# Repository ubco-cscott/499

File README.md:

# 499 Capstone Project - Group 16
Connor, Ellis, Nathan, Sarah, Sean

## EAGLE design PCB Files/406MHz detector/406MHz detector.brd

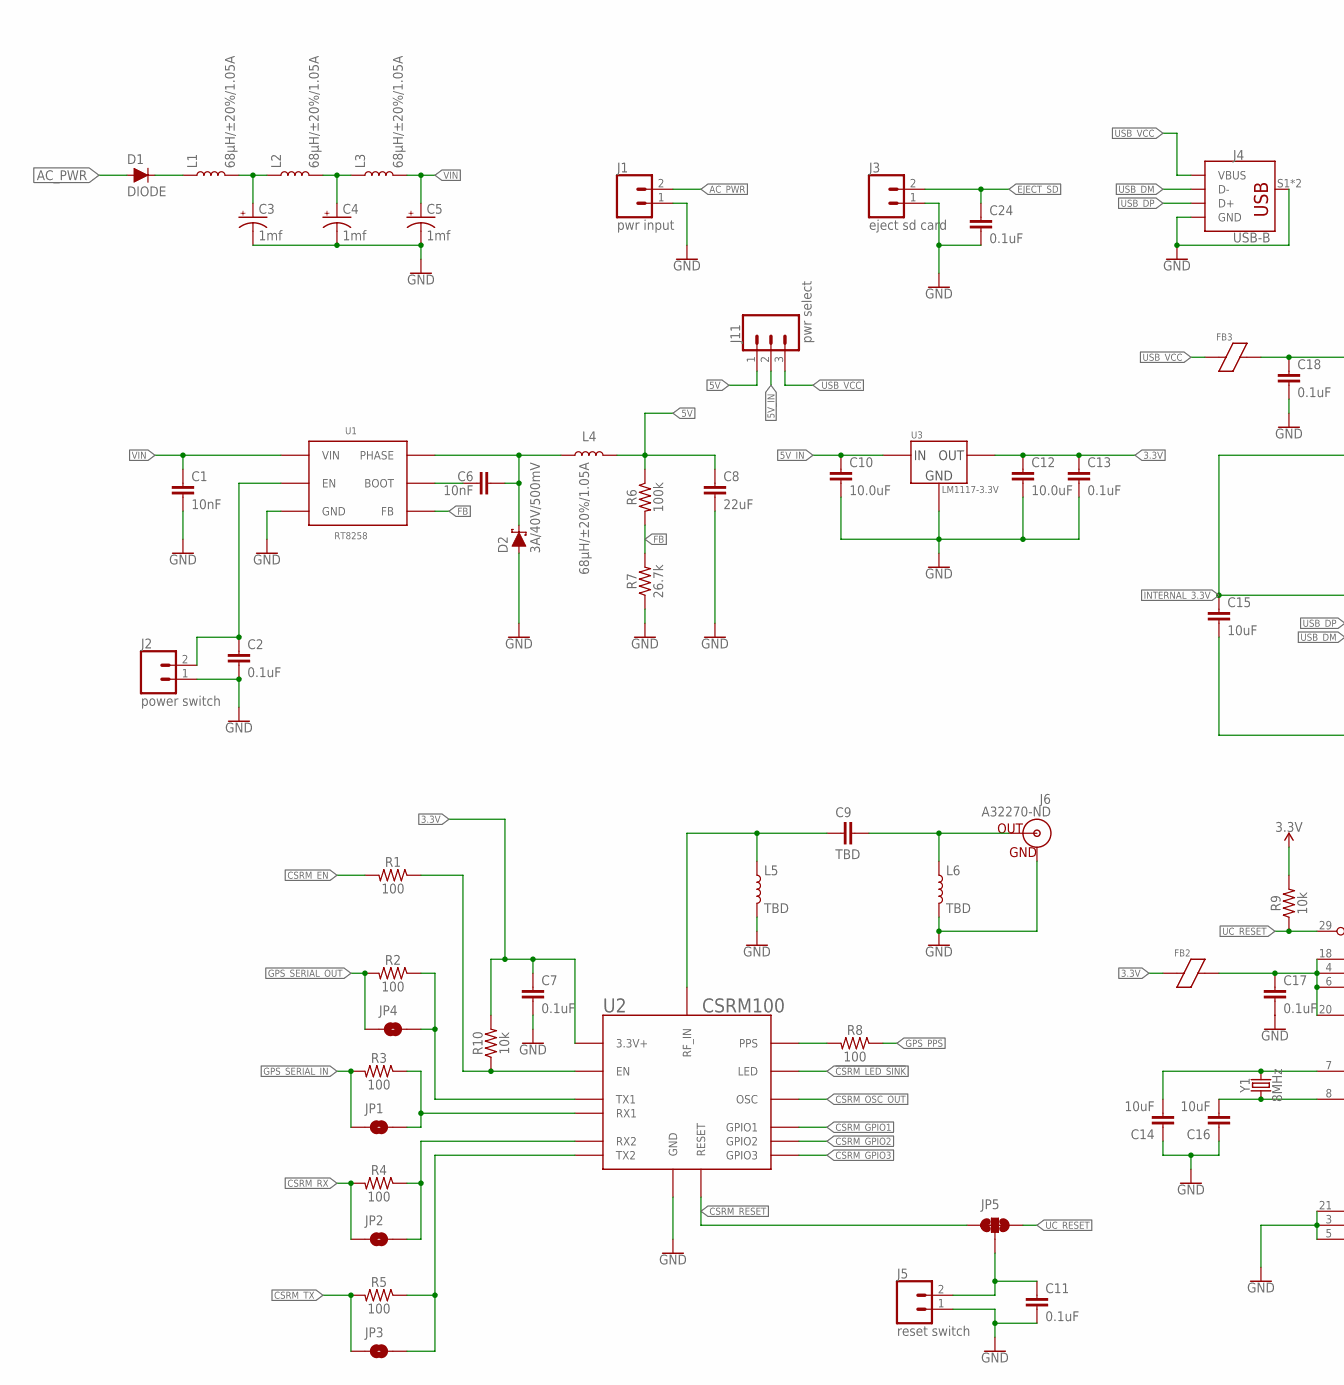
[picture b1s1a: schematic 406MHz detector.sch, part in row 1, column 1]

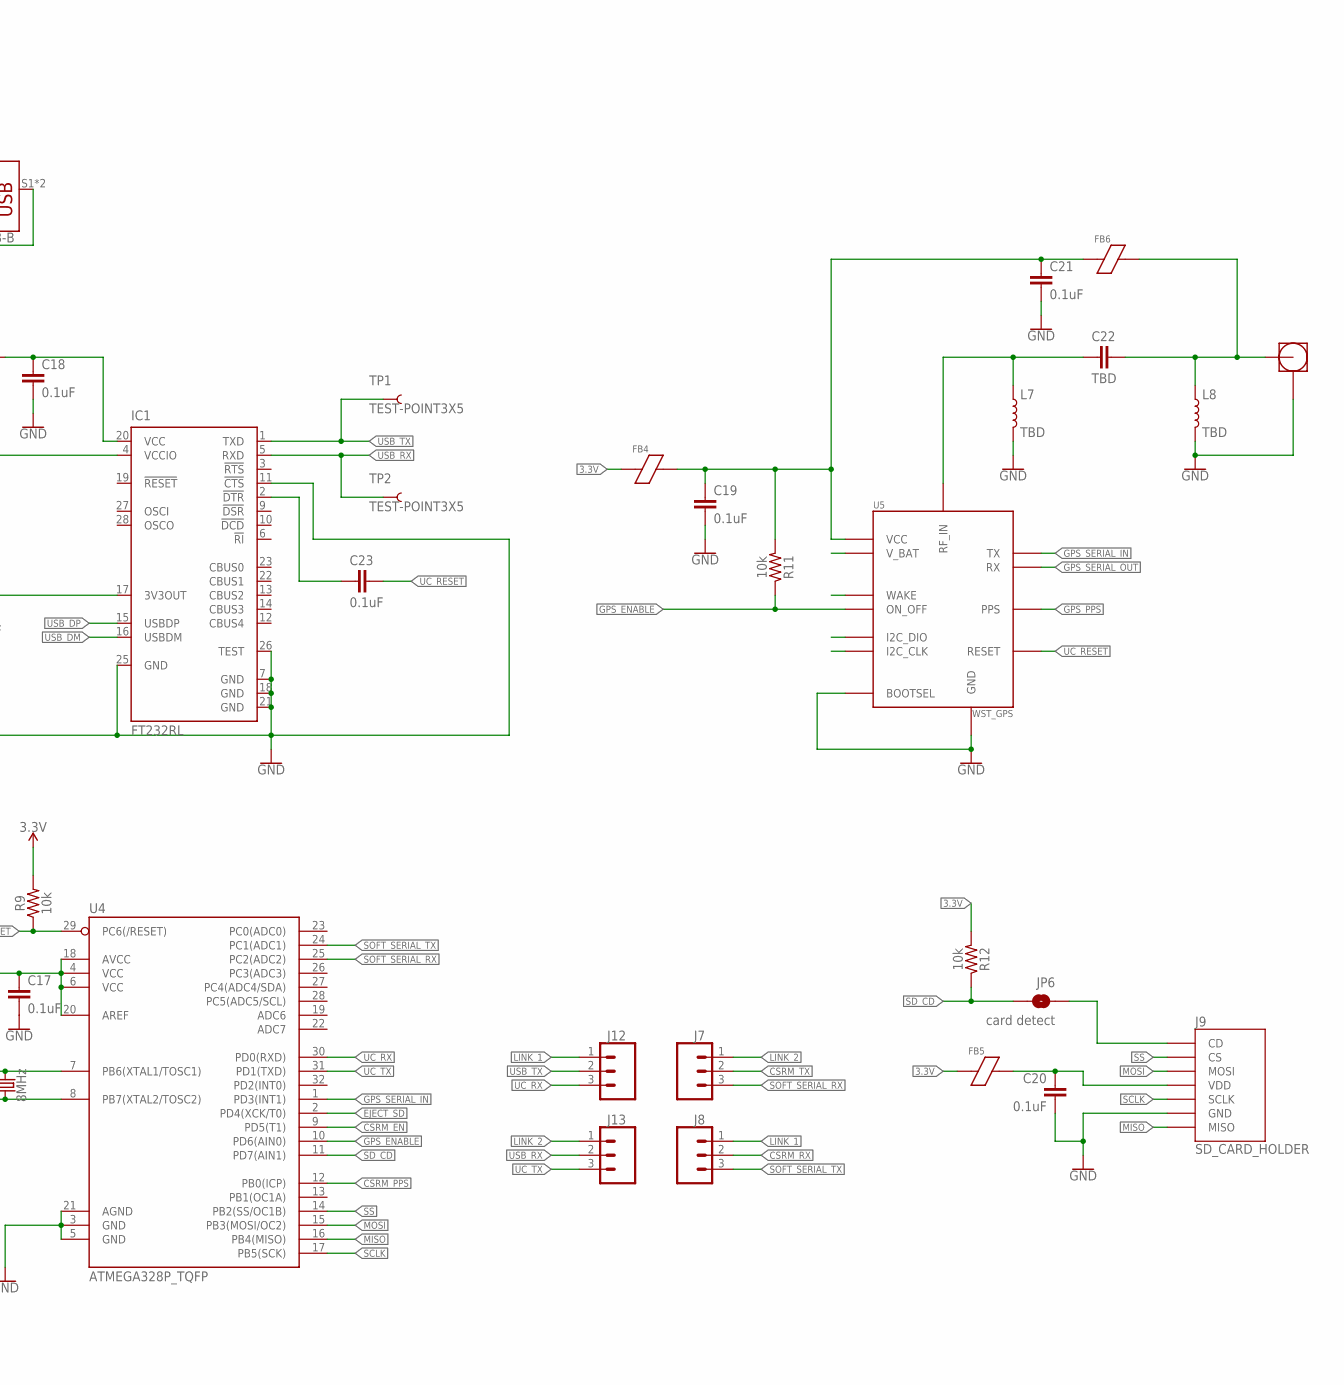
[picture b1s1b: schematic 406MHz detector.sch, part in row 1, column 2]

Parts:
C1, C6: 10nF; 0603
C2, C7, C11, C13, C17, C18, C19, C20, C21, C23, C24: 0.1uF; 0603
C3, C4, C5: 1mf; CPOL-RADIAL-5MM-10MM-KIT
C8: 22uF; 0603
C9, C22: TBD; 0603
C10, C12: 10.0uF; 1206
C14, C15, C16: 10uF; 1206
D1: DIODE; SMA-DIODE
D2: 3A/40V/500mV; SMA-DIODE
FB2, FB3, FB4, FB5, FB6: FERRITE_BEAD; 0603
IC1: FT232RL; SSOP28
J1: pwr input; 1X02_LOCK
J2: power switch; 1X02
J3: eject sd card; 1X02
J4: USB-B; USB
J5: reset switch; 1X02
J6: A32270-ND; A33270-ND
J7, J8, J12, J13: select jumper; 1X03_LOCK
J9: SD_CARD_HOLDER
J10: SMA; SMA_R/A
J11: pwr select; 1X03_LOCK
JP1, JP2, JP3, JP4: JUMPER-SMT_2_NO_SILK_ROUND; SMT-JUMPER_2_NO_SILK_ROUND
JP5: JUMPER-SMT_3_2-NC_TRACE_SILK; SMT-JUMPER_3_2-NC_TRACE_SILK
JP6: card detect; SMT-JUMPER_2_NO_SILK
L1, L2, L3, L4: 68µH/±20%/1.05A; CR75
L5, L6, L7, L8: TBD; 0603
R1, R2, R3, R4, R5, R8: 100; 0603
R6: 100k; 0603
R7: 26.7k; 0603
R9, R10, R11, R12: 10k; 0603
TP1, TP2: TEST-POINT3X5; PAD.03X.05
U1: RT8258; SOT23-6
U2: CSRM100; CSRM
U3: LM1117-3.3V; SOT223
U4: ATMEGA328P_TQFP; TQFP32-08
U5: WST_GPS
Y1: 8MHz; HC49UP

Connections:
3.3V: C7.1, C12.1, C13.1, FB2.1, FB4.1, FB5.1, R9.2, R10.2, R12.2, U2.PWR_IN (3.3V+), U3.2 (VOUT), U3.4 (VOUT)
5V: C8.1, J11.1, L4.P$2 (2), R6.1
5V_IN: C10.1, J11.2, U3.3 (VIN)
406_IN: C9.2, L5.1, U2.406_IN (RF_IN)
!CSRM_LED_SINK: U2.LED
AC_PWR: D1.A, J1.2
ANTENNA_CONNECTOR: C9.1, J6.OUT, L6.1
BOOT: C6.1, U1.1 (BOOT)
CSRM_EN: R1.2, U4.9 (PD5(T1))
CSRM_GPIO1: U2.GPIO1
CSRM_GPIO2: U2.GPIO2
CSRM_GPIO3: U2.GPIO3
CSRM_OSC_OUT: U2.OSC_OUT (OSC)
CSRM_PPS: R8.2, U2.PPS, U4.12 (PB0(ICP))
CSRM_RESET: JP5.1, U2._RESET (RESET)
CSRM_RX: J8.2, JP2.1, R4.2
CSRM_TX: J7.2, JP3.1, R5.2
EJECT_SD: C24.1, J3.2, U4.2 (PD4(XCK/T0))
FB: R6.2, R7.2, U1.3 (FB)
GND: C1.2, C2.2, C3.-, C4.-, C5.-, C7.2, C8.2, C10.2, C11.2, C12.2, C13.2, C14.1, C15.2, C16.1, C17.2, C18.2, C19.2, C20.2, C21.2, C24.2, D2.A, IC1.7 (GND), IC1.11 (!CTS), IC1.18 (GND), IC1.21 (GND), IC1.25 (GND), IC1.26 (TEST), J1.1, J2.1, J3.1, J4.4 (GND), J4.S1 (SHIELD), J4.S2 (SHIELD), J5.1, J6.GND1 (GND), J6.GND2 (GND), J6.GND3 (GND), J6.GND4 (GND), J9.GND1 (GND), J9.GND2 (GND), J9.P6 (GND), J10.P$2, J10.P$3, J10.P$4, J10.P$5, L5.2, L6.2, L7.2, L8.2, R7.1, U1.2 (GND), U2.GND, U2.GND1 (GND), U2.GND2 (GND), U2.GND3 (GND), U2.GND4 (GND), U3.1 (GND), U4.3 (GND), U4.5 (GND), U4.21 (AGND), U5.P$1 (GND), U5.P$3 (GND), U5.P$9 (BOOTSEL), U5.P$17 (GND), U5.P$18 (GND), U5.P$19 (GND)
GPS_ANTENNA: C22.2, L7.1, U5.P$2 (RF_IN)
GPS_CONNECTOR: C22.1, FB6.2, J10.P$1, L8.1
GPS_ENABLE: R11.1, U4.10 (PD6(AIN0)), U5.P$15 (ON_OFF)
GPS_PPS: R8.1, U5.P$14 (PPS)
GPS_SERIAL_IN: JP1.1, R3.2, U4.1 (PD3(INT1)), U5.P$10 (TX)
GPS_SERIAL_OUT: JP4.1, R2.2, U5.P$11 (RX)
HF_SWITCH: C6.2, D2.C, L4.P$1 (1), U1.6 (PHASE)
INTERNAL_3.3V: C15.1, IC1.4 (VCCIO), IC1.17 (3V3OUT)
LINK_1: J8.1, J12.1
LINK_2: J7.1, J13.1
MISO: J9.P7 (MISO), U4.16 (PB4(MISO))
MOSI: J9.P3 (MOSI), U4.15 (PB3(MOSI/OC2))
unnamed: JP4.2, R2.1, U2.TX1
unnamed: JP1.2, R3.1, U2.RX1
unnamed: JP2.2, R4.1, U2.RX2
unnamed: JP3.2, R5.1, U2.TX2
unnamed: R1.1, R10.1, U2.EN
unnamed: C23.1, IC1.2 (!DTR)
unnamed: J9.CD1 (CD), J9.CD2 (CD), JP6.1
unnamed: D1.C, L1.P$1 (1)
unnamed: C3.+, L1.P$2 (2), L2.P$1 (1)
unnamed: C4.+, L2.P$2 (2), L3.P$1 (1)
unnamed: C18.1, FB3.1, IC1.20 (VCC)
unnamed: C14.2, U4.7 (PB6(XTAL1/TOSC1)), Y1.2
unnamed: C16.2, U4.8 (PB7(XTAL2/TOSC2)), Y1.1
unnamed: C19.1, C21.1, FB4.2, FB6.1, R11.2, U5.P$5 (VCC)
unnamed: C17.1, FB2.2, U4.4 (VCC), U4.6 (VCC), U4.18 (AVCC), U4.20 (AREF)
unnamed: C20.1, FB5.2, J9.P4 (VDD)
RESET: C11.1, J5.2, JP5.2
SCLK: J9.P5 (SCLK), U4.17 (PB5(SCK))
SD_CD: JP6.2, R12.1, U4.11 (PD7(AIN1))
SOFT_SERIAL_RX: J7.3, U4.25 (PC2(ADC2))
SOFT_SERIAL_TX: J8.3, U4.24 (PC1(ADC1))
SS: J9.P2 (CS), U4.14 (PB2(SS/OC1B))
SUPPLY_ENABLE: C2.1, J2.2, U1.4 (EN)
UC_RESET: C23.2, JP5.3, R9.1, U4.29 (PC6(/RESET)), U5.P$4 (RESET)
UC_RX: J12.3, U4.30 (PD0(RXD))
UC_TX: J13.3, U4.31 (PD1(TXD))
USB_DM: IC1.16 (USBDM), J4.2 (D-)
USB_DP: IC1.15 (USBDP), J4.3 (D+)
USB_RX: IC1.5 (RXD), J13.2, TP2.P$1
USB_TX: IC1.1 (TXD), J12.2, TP1.P$1
USB_VCC: FB3.2, J4.1 (VBUS), J11.3
VIN: C1.1, C5.+, L3.P$2 (2), U1.5 (VIN)

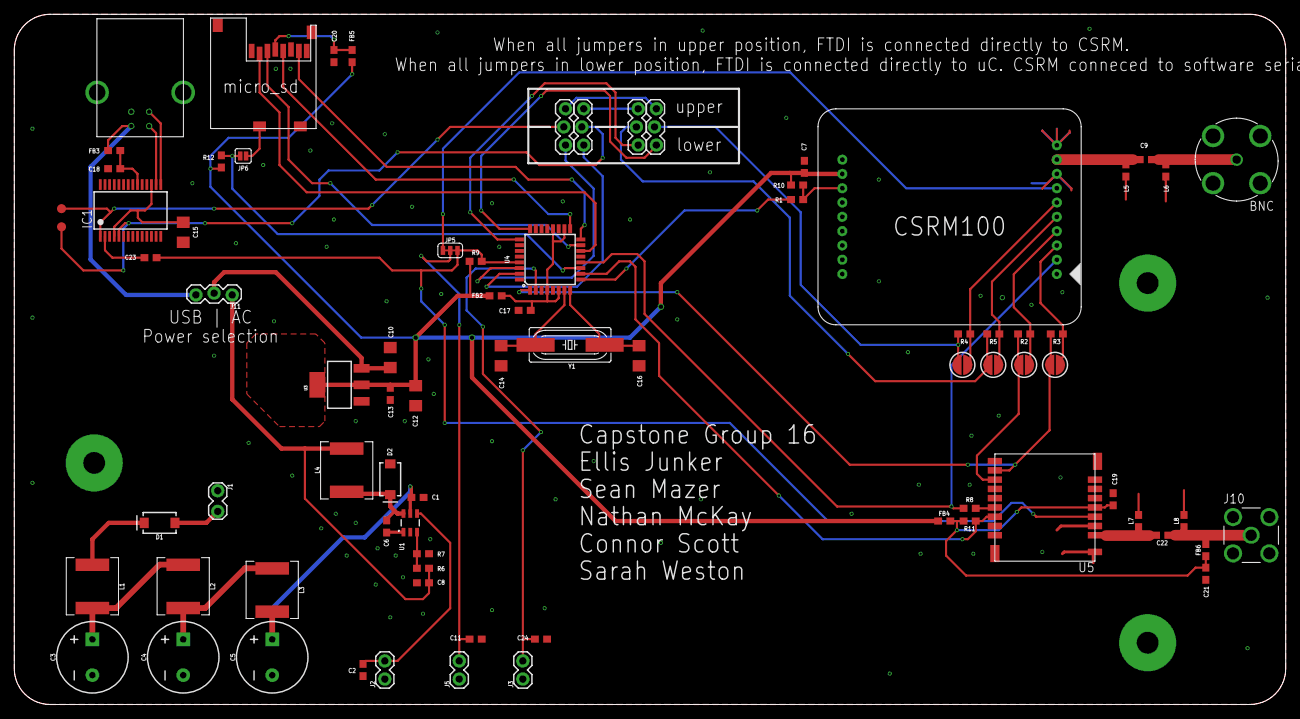
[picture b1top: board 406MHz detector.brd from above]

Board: 2 copper layers, 177.8 x 96.5 mm, 79 parts (0 on the bottom side), 59 nets.

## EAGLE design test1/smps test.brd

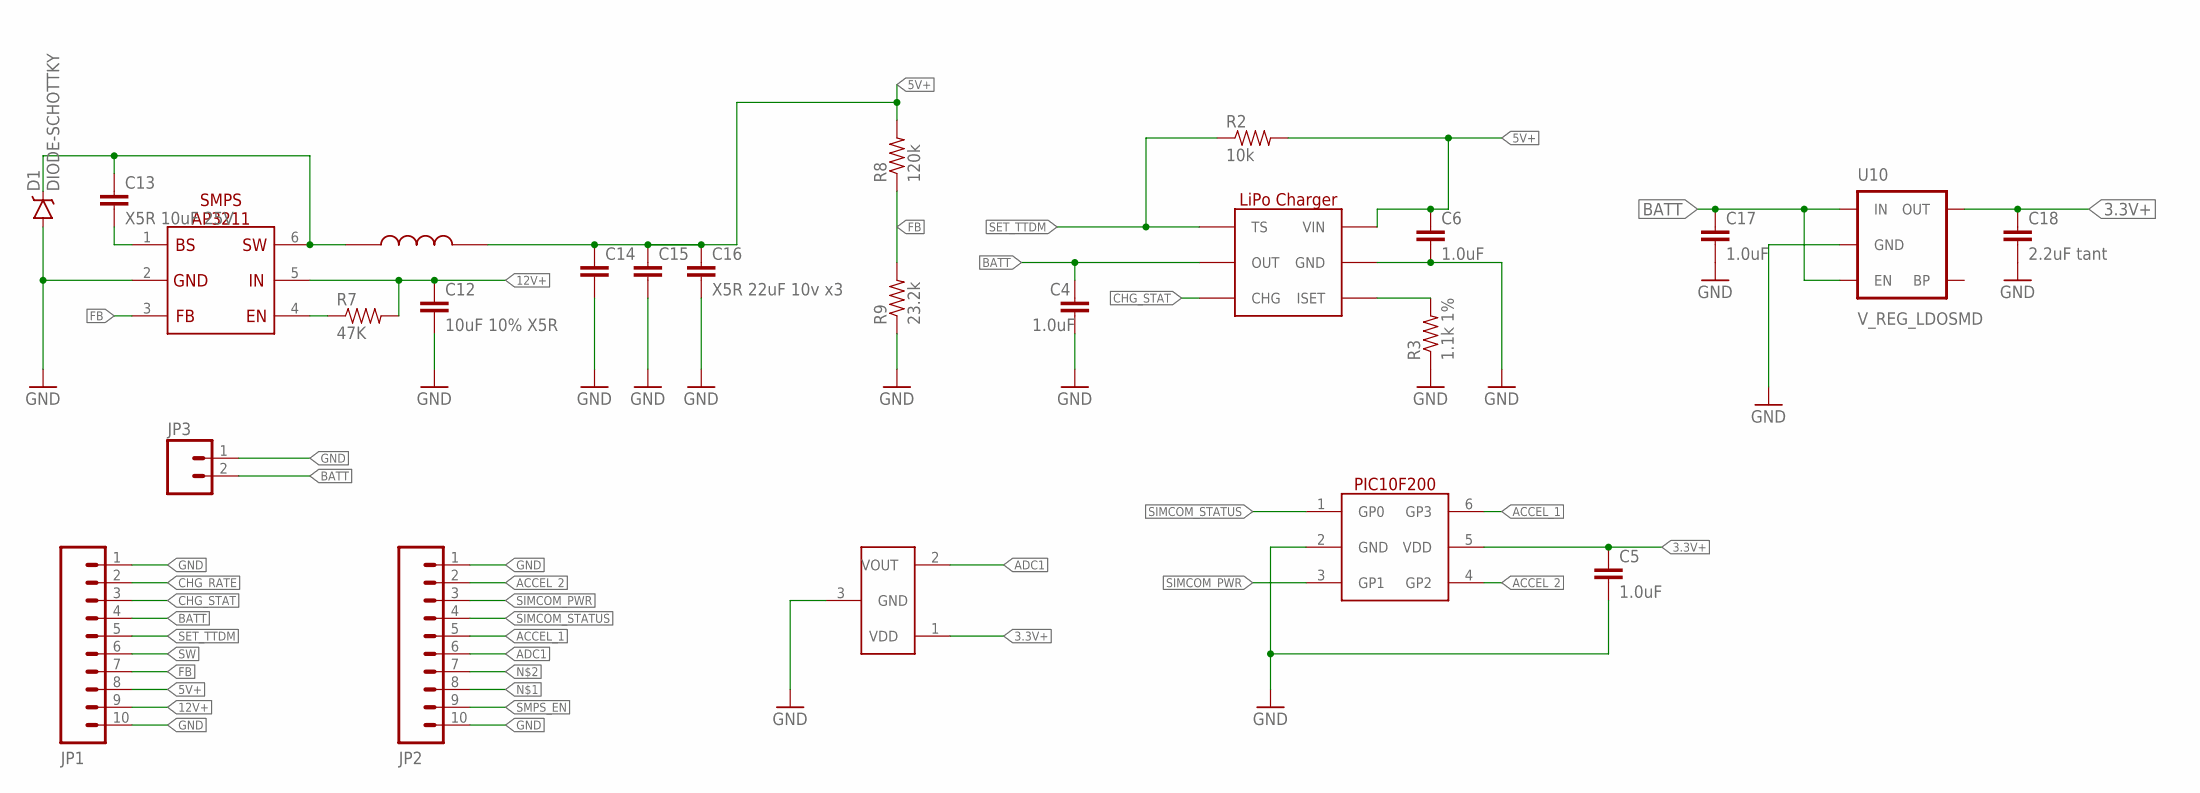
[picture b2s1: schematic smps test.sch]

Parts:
C4, C5, C6, C17: 1.0uF; 0603-CAP
C12: 10uF 10% X5R; 1206
C13: X5R 10uF 25V; 0603-CAP
C14, C15: CAP0603-CAP; 0603-CAP
C16: X5R 22uF 10v x3; 0603-CAP
C18: 2.2uF tant; 0603-CAP
D1: DIODE-SCHOTTKY; MICRO_SMP
JP1, JP2: M10LOCK; 1X10_LOCK
JP3: M02-JST-2MM-SMT; JST-2-SMD
R2: 10k; 0603-RES
R3: 1.1k 1%; 0603-RES
R7: 47K; 0603-RES
R8: 120k; 0603-RES
R9: 23.2k; 0603-RES
U3: BQ21040; SOT23-6
U6: PIC10F200; SOT23-6
U10: V_REG_LDOSMD; SOT23-5
U$1: MCP9700T-E; SOT23-3
U$2: AP3211; SOT23-6
U$4: INDUCTOR; INDUCTOR_FIXED

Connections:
3.3V+: C5.1, C18.1, U6.5 (VDD), U10.5 (OUT), U$1.1 (VDD)
5V+: C6.1, C14.1, C15.1, C16.1, JP1.8, R2.2, R8.2, U3.6 (VIN), U$4.P$2
12V+: C12.1, JP1.9, R7.2, U$2.5
ACCEL_1: JP2.5, U6.6 (GP3)
ACCEL_2: JP2.2, U6.4 (GP2)
ADC1: JP2.6, U$1.2 (VOUT)
BATT: C4.1, C17.1, JP1.4, JP3.2 (1), U3.2 (OUT), U10.1 (IN), U10.3 (EN)
CHG_RATE: JP1.2, R3.2, U3.4 (ISET)
CHG_STAT: JP1.3, U3.3 (CHG)
FB: JP1.7, R8.1, R9.2, U$2.3
GND: C4.2, C5.2, C6.2, C12.2, C14.2, C15.2, C16.2, C17.2, C18.2, D1.P$2 (A), JP1.1, JP1.10, JP2.1, JP2.10, JP3.1 (2), R3.1, R9.1, U3.5 (GND), U6.2 (GND), U10.2 (GND), U$1.3 (GND), U$2.2
unnamed: C13.2, U$2.1
SET_TTDM: JP1.5, R2.1, U3.1 (TS)
SIMCOM_PWR: JP2.3, U6.3 (GP1)
SIMCOM_STATUS: JP2.4, U6.1 (GP0)
SMPS_EN: JP2.9, R7.1, U$2.4
SW: C13.1, D1.P$1 (C), JP1.6, U$2.6, U$4.P$1

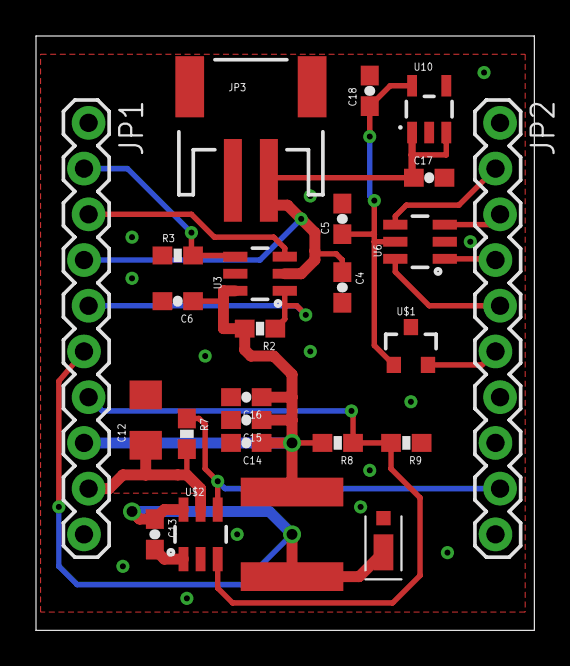
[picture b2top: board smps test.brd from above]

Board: 2 copper layers, 27.7 x 33.0 mm, 25 parts (0 on the bottom side), 17 nets.

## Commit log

2020-01-16 test.txt added
2020-01-16 note
2020-01-19 first update for pull test
2020-01-19 sarahs first change
2020-01-20 first push with real files
2020-01-20 eagle test board added
2020-01-20 changed the name of the example PCB folder
2020-01-21 added the PIC datasheet
2020-01-21 changed the readme
2020-01-21 eagle library and schematic updated
2020-01-21 I started on the converter
2020-01-22 Nathan made changes in 413 lecture finished the converter
2020-01-23 added a package that models the CSRM100 receiver in library labaled capstone L1
2020-01-25 added CSRM100 to capstone library, and schematic
2020-01-26 testing connor's branch
2020-01-26 added branches for Nathan and Sarah
2020-01-26 cleaned up some traces
2020-01-26 cleaning up repo
2020-01-26 fixed ignore files list
2020-01-26 added library backups to ignored files list
2020-01-26 removed library backup files
2020-01-27 added led example
2020-01-27 added a microcontroller
2020-01-27 added led example nets
2020-01-27 nets drawn
2020-01-27 added some nets
2020-01-27 added seperate schematic areas for git merging
2020-01-27 removed sample led changes
2020-01-27 copied from master
2020-01-28 cleaning up branches
2020-01-28 added boxes and labels to schematic for separating workspaces
2020-01-28 removed problem with ground labels connecting to 3.3V net
2020-01-28 added capactior to sw_reg enable input
2020-01-28 added sw_reg datasheet, renamed pic33 datashee
2020-01-28 added diode datasheet, added input filtering for aircraft power
2020-01-28 connor updating files
2020-02-04 changed uc, added crystal
2020-02-04 added picture of pinout
2020-02-05 components added to schematic
2020-02-06 added photo of microSD pinout
2020-02-08 added ftdi adaptor, small schematic changes
2020-02-08 small changes to PCB
2020-02-09 added labels to usb pins
2020-02-09 removed old footprints from library, added usb connector
2020-02-09 added gps module to schematic
2020-02-11 latest version of sch and brd
2020-02-11 added SMA jack datasheet
2020-02-12 ensuring updates are pushed
2020-02-12 latest update of schematic, sent to kevin for double check
2020-02-12 added p/n for ferrite bead
2020-02-14 library changes, schematic changes, board changes
2020-02-15 final version of PCB to review
2020-03-11 sd card logger added
2020-03-17 added arduino code
2020-03-22 new arduino sketch
2020-04-02 added my update
2020-04-08 added satellite data

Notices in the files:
parts and their libraries:
SparkFun-Capacitors: Licensing: Creative Commons ShareAlike 4.0 International - https://creativecommons.org/licenses/by-sa/4.0
